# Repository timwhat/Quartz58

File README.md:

# Quartz58

Attempt at a two places removed, no compromises keyboard

Inspired by the lily58, SoflePLUS2, and MANY others to fit my personal needs

## Images

### CAD

Exploded view of the CAD currently

### PCB

BASE!

### Schematic

The reason why I made this project was that I was always fascinated by keyboards, especially the ergonomic ones, and I just love designing things. So since this was my chance to try it, so I jumped at it!

## Features

### Key Features

- **58 keys**, each able to support at the same time, MX and Choc hotswap sockets!

- **Wireless**, with the power of a nice!nano clone and a 750mAh battery!

- **iPod-style Encoder** on the left side for any encoder needed jazz... (such as volume control)

- **Trackpad** on the right side, for any analog needed or gesture related jazz pt2... (such as precision or window management)

- **Gasket Mount**, for improved typing feel and acoustics

- **MagSafe Magnets**, for adjustable tenting and compatibility with existing MagSafe accessories!

- **nice!view and OLED Display Support** on both halves to show stats like battery life, WPM, connection status, etc...

## Development Log

See [JOURNAL.md](JOURNAL.md) for detailed development progress and decisions

## BOM

| Purchase Status | Part                                                          | Qty | Price/per (CAD) | Total      | Link                                                                                            | Shipping (CAD) | Notes                                                                                 |
| --------------- | ------------------------------------------------------------- | --- | --------------- | ---------- | ----------------------------------------------------------------------------------------------- | -------------- | ------------------------------------------------------------------------------------- |
| x               | 10cm 10p 0.5mm pitch 10PCS FPC FFC Ribbon Flexible Flat Cable | 1   | 7.45            | 7.45       | [link](https://www.aliexpress.com/item/1005006420267064.html)                                   | 0              |                                                                                       |
| x               | 10cm 6p 0.5mm pitch 10PCS FPC FFC Ribbon Flexible Flat Cable  | 1   | 7.44            | 7.44       | [link](https://www.aliexpress.com/item/1005006420267064.html)                                   | 0              |                                                                                       |
| x               | Breakable Stackable PCB IC Crystal Socket Connector (for mcu) | 1   | 3.66            | 3.66       | [link](https://www.aliexpress.com/item/4001122376295.html)                                      | 0              |                                                                                       |
| x               | Nice View                                                     | 1   | 23.58           | 23.58      | [link](https://www.aliexpress.com/item/1005008115497843.html)                                   | 0              |                                                                                       |
| x               | 6 pin FFC FPC Connector 0.5 (10 per pack)                     | 1   | 2.05            | 2.05       | [link](https://www.aliexpress.com/item/10000348360254.html)                                     | 0              |                                                                                       |
| x               | 10 pin FFC FPC Connector 0.5 (10 per pack)                    | 1   | 2.06            | 2.06       | [link](https://www.aliexpress.com/item/10000348360254.html)                                     | 0              |                                                                                       |
| x               | Kailh Hot-swappable PCB Socket Hot Plug                       | 1   | 5.89            | 5.89       | [link](https://www.aliexpress.com/item/1005007225352311.html)                                   | 0              | Already have 20                                                                       |
| x               | M2 (OD3.2mm) 50pcs x 2mm                                      | 1   | 3.02            | 3.02       | [link](https://www.aliexpress.com/item/1005005220632314.html)                                   | 0              |                                                                                       |
| x               | White Blank MDA keycap set                                    | 1   | 37.79           | 37.79      | [link](https://www.aliexpress.com/item/1005007747757142.html)                                   | 0              |                                                                                       |
| x               | Reset Button                                                  | 1   | 3.21            | 3.21       | [link](https://www.aliexpress.com/item/33032223116.html)                                        | 0              |                                                                                       |
| x               | Power Switch                                                  | 1   | 3.07            | 3.07       | [link](https://www.aliexpress.com/item/4000685483225.html)                                      | 0              |                                                                                       |
| x               | Battery Jack (5 per pack)                                     | 1   | 1.79            | 1.79       | [link](https://www.aliexpress.com/item/1005002564191148.html)                                   | 0              | Used this for increased flexibility in use in the keyboard instead of the normal jack |
| x               | Magsafe Magnet Rings 15 plus version (2 per pack)             | 1   | 5.49            | 5.49       | [link](https://www.aliexpress.com/item/1005006981590979.html)                                   | 0              |                                                                                       |
| x               | 404090 2000mAh Battery                                        | 2   | 7.49            | 14.98      | [link](https://www.aliexpress.com/item/1005009607827493.html?mp=1)                              | 10.27          |                                                                                       |
| x               | TPS65-201A-S                                                  | 1   | 8.93            | 8.93       | [link](https://www.mouser.ca/ProductDetail/Azoteq/TPS65-201A-S?qs=pfd5qewlna5Lh8O0E8DcUQ%3D%3D) | 20             |                                                                                       |
| x               | PCB from JLCPCB                                               | 1   | 23.45           | 23.45      | [link](https://cart.jlcpcb.com/quote?rand=0.04393028142638511)                                  | 16.54          |                                                                                       |
|                 |                                                               |     |                 |            |                                                                                                 |                |                                                                                       |
|                 | **Subtotal:**                                                 |     | **CAD:**        | **153.86** |                                                                                                 | **46.81**      |                                                                                       |
|                 |                                                               |     | USD             | 111.21     |                                                                                                 | 33.84          |                                                                                       |
|                 |                                                               |     | **Total:**      | **145.05** |                                                                                                 |                | Will make up the difference if there are any hidden costs                             |
|                 |                                                               |     |                 |            |                                                                                                 |                |                                                                                       |

### Stuff I will buy

| Purchase Status | Part                                             | Qty | Price/per (CAD) | Total | Link                                                               | Shipping (CAD) | Notes |
| --------------- | ------------------------------------------------ | --- | --------------- | ----- | ------------------------------------------------------------------ | -------------- | ----- |
| x               | 20 PCS 2MM Thick Mechanical Keyboard Gasket      | 1   | 7.4             | 7.4   | [link](https://www.aliexpress.com/item/1005004800667967.html)      | 0              |       |
|                 | TTC Frozen V2 Switch Silent Linear (60 per pack) | 1   | 36.58           | 36.58 | [link](https://www.aliexpress.com/item/1005008909952057.html)      | 0              |       |
|                 | M2x16mm Hex Socket Head Cap                      | 1   | 2.9             | 2.9   | [link](http://www.aliexpress.com/item/32810872544.html)            | 0              |       |
| x               | NRF52840                                         | 2   | 4.32            | 8.64  | [link](https://www.aliexpress.com/item/1005006271779544.html?mp=1) | 0              |       |
| x               | SOD-123                                          | 1   | 2.79            | 2.79  | [link](https://www.aliexpress.com/item/1005006323468521.html)      | 0              |       |

### These are the stuff that I will get at a later date

| Part           | Qty | Price/per (CAD) | Total | Link  | Shipping (CAD) | Notes                                                     |
| -------------- | --- | --------------- | ----- | ----- | -------------- | --------------------------------------------------------- |
| TSWB3NCB111LFS | 1   | 14.54           | 14.54 | XCMKB | 48.48          | This is a custom order to them as they ship from malasyia |

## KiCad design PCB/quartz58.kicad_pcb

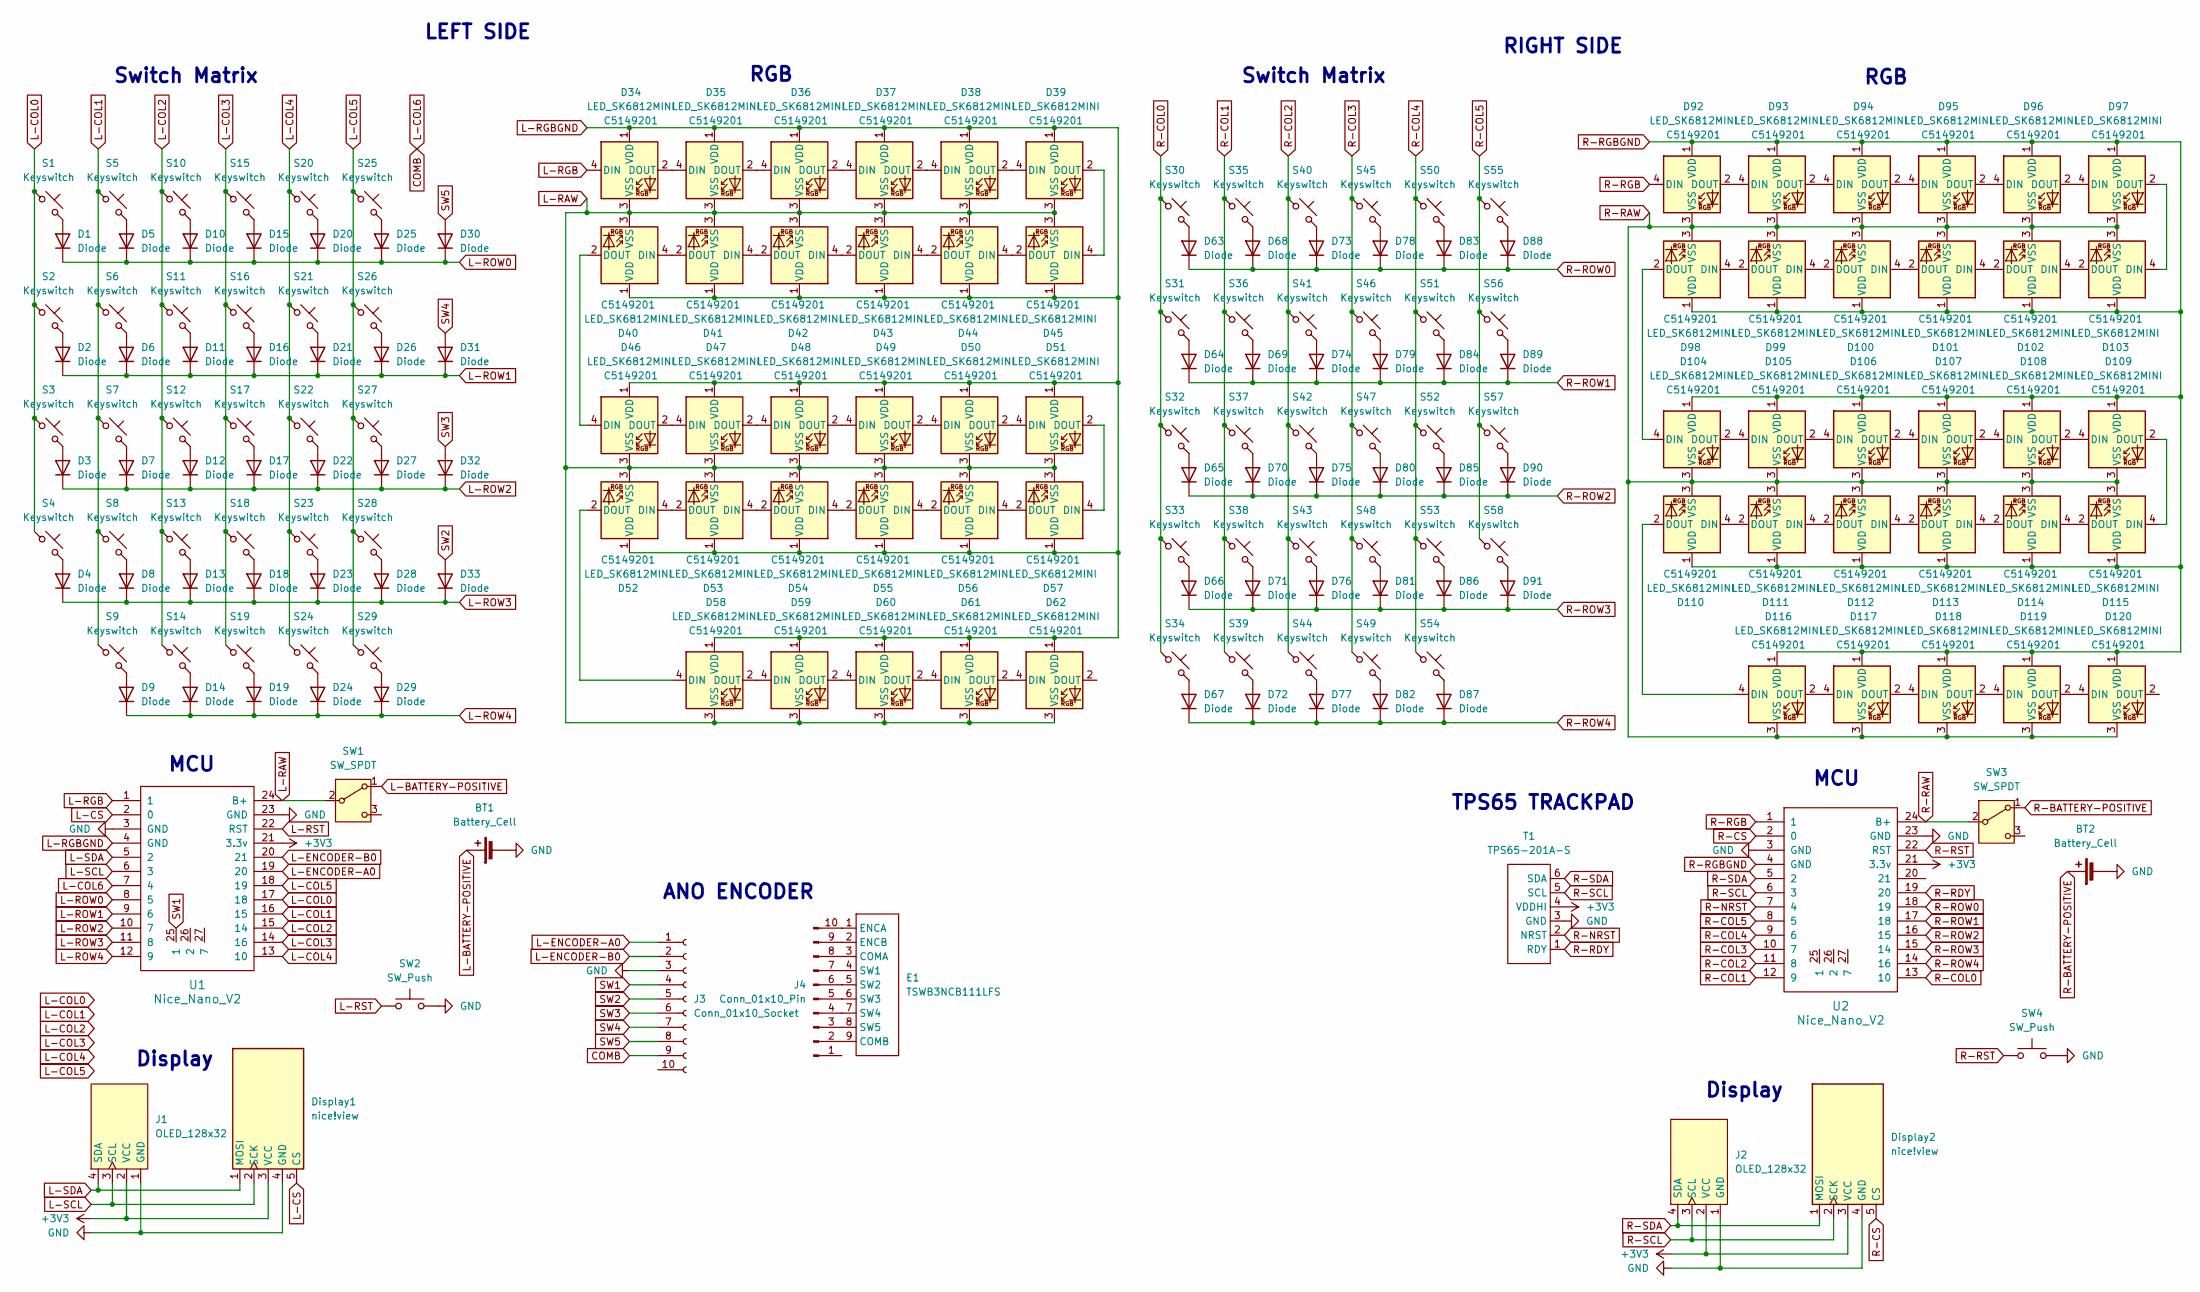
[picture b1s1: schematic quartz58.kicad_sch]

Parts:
BT1, BT2: Battery_Cell; JST_PH_S2B-PH-K_1x02_P2.00mm_Horizontal
D1, D2, D3, D4, D5, D6, D7, D8, D9, D10, D11, D12, D13, D14, D15, D16, D17, D18, D19, D20, D21, D22, D23, D24, D25, D26, D27, D28, D29, D30, D31, D32, D33, D63, D64, D65, D66, D67, D68, D69, D70, D71, D72, D73, D74, D75, D76, D77, D78, D79, D80, D81, D82, D83, D84, D85, D86, D87, D88, D89, D90, D91: Diode; Diode_SOD-123
D34, D35, D36, D37, D38, D39, D40, D41, D42, D43, D44, D45, D46, D47, D48, D49, D50, D51, D52, D53, D54, D55, D56, D57, D58, D59, D60, D61, D62, D92, D93, D94, D95, D96, D97, D98, D99, D100, D101, D102, D103, D104, D105, D106, D107, D108, D109, D110, D111, D112, D113, D114, D115, D116, D117, D118, D119, D120: LED_SK6812MINI; SK6812-MINI-E; LCSC C5149201
Display1, Display2: nice!view; nice_view
E1: TSWB3NCB111LFS; Encoder_TSWB3NCB111LFS
J1, J2: OLED_128x32
J3: Conn_01x10_Socket; Hirose_FH12-10S-0.5SH_1x10-1MP_P0.50mm_Horizontal
J4: Conn_01x10_Pin; Hirose_FH12-10S-0.5SH_1x10-1MP_P0.50mm_Horizontal
S1, S2, S3, S4, S5, S6, S7, S8, S9, S10, S11, S12, S13, S14, S15, S16, S17, S18, S19, S20, S21, S22, S23, S24, S25, S26, S27, S28, S29, S30, S31, S32, S33, S34, S35, S36, S37, S38, S39, S40, S41, S42, S43, S44, S45, S46, S47, S48, S49, S50, S51, S52, S53, S54, S55, S56, S57, S58: Keyswitch; Hotswap_Choc_V1V2
SW1, SW3: SW_SPDT; SW_SSSS811101
SW2, SW4: SW_Push; SW_EVQPUJ_4P7X3P5_PAN
T1: TPS65-201A-S; Hirose_FH12-6S-0.5SH_1x06-1MP_P0.50mm_Horizontal
U1, U2: Nice_Nano_V2; Nice_Nano_V2_Flipped

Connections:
+3V3: Display1.3 (VCC), Display2.3 (VCC), J1.2 (VCC), J2.2 (VCC), T1.4 (VDDHI), U1.21 (3.3v), U2.21 (3.3v)
COMB: J3.9, U1.7 (4)
GND: BT1.2 (-), BT2.2 (-), Display1.4 (GND), Display2.4 (GND), J1.1 (GND), J2.1 (GND), J3.3, SW2.2, SW4.2, T1.3 (GND), U1.3 (GND), U1.23 (GND), U2.3 (GND), U2.23 (GND)
L-BATTERY-POSITIVE: BT1.1 (+), SW1.1 (A)
L-COL0: S1.1, S2.1, S3.1, S4.1, U1.17 (18)
L-COL1: S5.1, S6.1, S7.1, S8.1, S9.1, U1.16 (15)
L-COL2: S10.1, S11.1, S12.1, S13.1, S14.1, U1.15 (14)
L-COL3: S15.1, S16.1, S17.1, S18.1, S19.1, U1.14 (16)
L-COL4: S20.1, S21.1, S22.1, S23.1, S24.1, U1.13 (10)
L-COL5: S25.1, S26.1, S27.1, S28.1, S29.1, U1.18 (19)
L-CS: Display1.5 (CS), U1.2 (0)
L-ENCODER-A0: J3.1, U1.19 (20)
L-ENCODER-B0: J3.2, U1.20 (21)
L-RAW: D34.3 (VSS), D35.3 (VSS), D36.3 (VSS), D37.3 (VSS), D38.3 (VSS), D39.3 (VSS), D40.3 (VSS), D41.3 (VSS), D42.3 (VSS), D43.3 (VSS), D44.3 (VSS), D45.3 (VSS), D46.3 (VSS), D47.3 (VSS), D48.3 (VSS), D49.3 (VSS), D50.3 (VSS), D51.3 (VSS), D52.3 (VSS), D53.3 (VSS), D54.3 (VSS), D55.3 (VSS), D56.3 (VSS), D57.3 (VSS), D58.3 (VSS), D59.3 (VSS), D60.3 (VSS), D61.3 (VSS), D62.3 (VSS), SW1.2 (B), U1.24 (B+)
L-RGB: D34.4 (DIN), U1.1
L-RGBGND: D34.1 (VDD), D35.1 (VDD), D36.1 (VDD), D37.1 (VDD), D38.1 (VDD), D39.1 (VDD), D40.1 (VDD), D41.1 (VDD), D42.1 (VDD), D43.1 (VDD), D44.1 (VDD), D45.1 (VDD), D46.1 (VDD), D47.1 (VDD), D48.1 (VDD), D49.1 (VDD), D50.1 (VDD), D51.1 (VDD), D52.1 (VDD), D53.1 (VDD), D54.1 (VDD), D55.1 (VDD), D56.1 (VDD), D57.1 (VDD), D58.1 (VDD), D59.1 (VDD), D60.1 (VDD), D61.1 (VDD), D62.1 (VDD), U1.4 (GND)
L-ROW0: D1.1 (K), D5.1 (K), D10.1 (K), D15.1 (K), D20.1 (K), D25.1 (K), D30.1 (K), U1.8 (5)
L-ROW1: D2.1 (K), D6.1 (K), D11.1 (K), D16.1 (K), D21.1 (K), D26.1 (K), D31.1 (K), U1.9 (6)
L-ROW2: D3.1 (K), D7.1 (K), D12.1 (K), D17.1 (K), D22.1 (K), D27.1 (K), D32.1 (K), U1.10 (7)
L-ROW3: D4.1 (K), D8.1 (K), D13.1 (K), D18.1 (K), D23.1 (K), D28.1 (K), D33.1 (K), U1.11 (8)
L-ROW4: D9.1 (K), D14.1 (K), D19.1 (K), D24.1 (K), D29.1 (K), U1.12 (9)
L-RST: SW2.1, U1.22 (RST)
L-SCL: Display1.2 (SCK), J1.3 (SCL), U1.6 (3)
L-SDA: Display1.1 (MOSI), J1.4 (SDA), U1.5 (2)
unnamed: D1.2 (A), S1.2
unnamed: D2.2 (A), S2.2
unnamed: D3.2 (A), S3.2
unnamed: D4.2 (A), S4.2
unnamed: D5.2 (A), S5.2
unnamed: D6.2 (A), S6.2
unnamed: D7.2 (A), S7.2
unnamed: D8.2 (A), S8.2
unnamed: D9.2 (A), S9.2
unnamed: D10.2 (A), S10.2
unnamed: D11.2 (A), S11.2
unnamed: D12.2 (A), S12.2
unnamed: D13.2 (A), S13.2
unnamed: D14.2 (A), S14.2
unnamed: D15.2 (A), S15.2
unnamed: D16.2 (A), S16.2
unnamed: D17.2 (A), S17.2
unnamed: D18.2 (A), S18.2
unnamed: D19.2 (A), S19.2
unnamed: D20.2 (A), S20.2
unnamed: D21.2 (A), S21.2
unnamed: D22.2 (A), S22.2
unnamed: D23.2 (A), S23.2
unnamed: D24.2 (A), S24.2
unnamed: D25.2 (A), S25.2
unnamed: D26.2 (A), S26.2
unnamed: D27.2 (A), S27.2
unnamed: D28.2 (A), S28.2
unnamed: D29.2 (A), S29.2
unnamed: D34.2 (DOUT), D35.4 (DIN)
unnamed: D35.2 (DOUT), D36.4 (DIN)
unnamed: D36.2 (DOUT), D37.4 (DIN)
unnamed: D37.2 (DOUT), D38.4 (DIN)
unnamed: D38.2 (DOUT), D39.4 (DIN)
unnamed: D39.2 (DOUT), D45.4 (DIN)
unnamed: D40.4 (DIN), D41.2 (DOUT)
unnamed: D40.2 (DOUT), D46.4 (DIN)
unnamed: D41.4 (DIN), D42.2 (DOUT)
unnamed: D42.4 (DIN), D43.2 (DOUT)
unnamed: D43.4 (DIN), D44.2 (DOUT)
unnamed: D44.4 (DIN), D45.2 (DOUT)
unnamed: D46.2 (DOUT), D47.4 (DIN)
unnamed: D47.2 (DOUT), D48.4 (DIN)
unnamed: D48.2 (DOUT), D49.4 (DIN)
unnamed: D49.2 (DOUT), D50.4 (DIN)
unnamed: D50.2 (DOUT), D51.4 (DIN)
unnamed: D51.2 (DOUT), D57.4 (DIN)
unnamed: D52.4 (DIN), D53.2 (DOUT)
unnamed: D52.2 (DOUT), D58.4 (DIN)
unnamed: D53.4 (DIN), D54.2 (DOUT)
unnamed: D54.4 (DIN), D55.2 (DOUT)
unnamed: D55.4 (DIN), D56.2 (DOUT)
unnamed: D56.4 (DIN), D57.2 (DOUT)
unnamed: D58.2 (DOUT), D59.4 (DIN)
unnamed: D59.2 (DOUT), D60.4 (DIN)
unnamed: D60.2 (DOUT), D61.4 (DIN)
unnamed: D61.2 (DOUT), D62.4 (DIN)
unnamed: D63.2 (A), S30.2
unnamed: D64.2 (A), S31.2
unnamed: D65.2 (A), S32.2
unnamed: D66.2 (A), S33.2
unnamed: D67.2 (A), S34.2
unnamed: D68.2 (A), S35.2
unnamed: D69.2 (A), S36.2
unnamed: D70.2 (A), S37.2
unnamed: D71.2 (A), S38.2
unnamed: D72.2 (A), S39.2
unnamed: D73.2 (A), S40.2
unnamed: D74.2 (A), S41.2
unnamed: D75.2 (A), S42.2
unnamed: D76.2 (A), S43.2
unnamed: D77.2 (A), S44.2
unnamed: D78.2 (A), S45.2
unnamed: D79.2 (A), S46.2
unnamed: D80.2 (A), S47.2
unnamed: D81.2 (A), S48.2
unnamed: D82.2 (A), S49.2
unnamed: D83.2 (A), S50.2
unnamed: D84.2 (A), S51.2
unnamed: D85.2 (A), S52.2
unnamed: D86.2 (A), S53.2
unnamed: D87.2 (A), S54.2
unnamed: D88.2 (A), S55.2
unnamed: D89.2 (A), S56.2
unnamed: D90.2 (A), S57.2
unnamed: D91.2 (A), S58.2
unnamed: D92.2 (DOUT), D93.4 (DIN)
unnamed: D93.2 (DOUT), D94.4 (DIN)
unnamed: D94.2 (DOUT), D95.4 (DIN)
unnamed: D95.2 (DOUT), D96.4 (DIN)
unnamed: D96.2 (DOUT), D97.4 (DIN)
unnamed: D98.4 (DIN), D99.2 (DOUT)
unnamed: D100.4 (DIN), D101.2 (DOUT)
unnamed: D99.4 (DIN), D100.2 (DOUT)
unnamed: D101.4 (DIN), D102.2 (DOUT)
unnamed: D102.4 (DIN), D103.2 (DOUT)
unnamed: D97.2 (DOUT), D103.4 (DIN)
unnamed: D98.2 (DOUT), D104.4 (DIN)
unnamed: D104.2 (DOUT), D105.4 (DIN)
unnamed: D105.2 (DOUT), D106.4 (DIN)
unnamed: D106.2 (DOUT), D107.4 (DIN)
unnamed: D107.2 (DOUT), D108.4 (DIN)
unnamed: D108.2 (DOUT), D109.4 (DIN)
unnamed: D109.2 (DOUT), D115.4 (DIN)
unnamed: D110.4 (DIN), D111.2 (DOUT)
unnamed: D110.2 (DOUT), D116.4 (DIN)
unnamed: D111.4 (DIN), D112.2 (DOUT)
unnamed: D112.4 (DIN), D113.2 (DOUT)
unnamed: D113.4 (DIN), D114.2 (DOUT)
unnamed: D114.4 (DIN), D115.2 (DOUT)
unnamed: D116.2 (DOUT), D117.4 (DIN)
unnamed: D117.2 (DOUT), D118.4 (DIN)
unnamed: D118.2 (DOUT), D119.4 (DIN)
unnamed: D119.2 (DOUT), D120.4 (DIN)
unnamed: E1.3 (COMA), J4.8
unnamed: E1.9 (COMB), J4.2
unnamed: E1.1 (ENCA), J4.10
unnamed: E1.2 (ENCB), J4.9
unnamed: E1.4 (SW1), J4.7
unnamed: E1.5 (SW2), J4.6
unnamed: E1.6 (SW3), J4.5
unnamed: E1.7 (SW4), J4.4
unnamed: E1.8 (SW5), J4.3
R-BATTERY-POSITIVE: BT2.1 (+), SW3.1 (A)
R-COL0: S30.1, S31.1, S32.1, S33.1, S34.1, U2.13 (10)
R-COL1: S35.1, S36.1, S37.1, S38.1, S39.1, U2.12 (9)
R-COL2: S40.1, S41.1, S42.1, S43.1, S44.1, U2.11 (8)
R-COL3: S45.1, S46.1, S47.1, S48.1, S49.1, U2.10 (7)
R-COL4: S50.1, S51.1, S52.1, S53.1, S54.1, U2.9 (6)
R-COL5: S55.1, S56.1, S57.1, S58.1, U2.8 (5)
R-CS: Display2.5 (CS), U2.2 (0)
R-NRST: T1.2 (NRST), U2.7 (4)
R-RAW: D92.3 (VSS), D93.3 (VSS), D94.3 (VSS), D95.3 (VSS), D96.3 (VSS), D97.3 (VSS), D98.3 (VSS), D99.3 (VSS), D100.3 (VSS), D101.3 (VSS), D102.3 (VSS), D103.3 (VSS), D104.3 (VSS), D105.3 (VSS), D106.3 (VSS), D107.3 (VSS), D108.3 (VSS), D109.3 (VSS), D110.3 (VSS), D111.3 (VSS), D112.3 (VSS), D113.3 (VSS), D114.3 (VSS), D115.3 (VSS), D116.3 (VSS), D117.3 (VSS), D118.3 (VSS), D119.3 (VSS), D120.3 (VSS), SW3.2 (B), U2.24 (B+)
R-RDY: T1.1 (RDY), U2.19 (20)
R-RGB: D92.4 (DIN), U2.1
R-RGBGND: D92.1 (VDD), D93.1 (VDD), D94.1 (VDD), D95.1 (VDD), D96.1 (VDD), D97.1 (VDD), D98.1 (VDD), D99.1 (VDD), D100.1 (VDD), D101.1 (VDD), D102.1 (VDD), D103.1 (VDD), D104.1 (VDD), D105.1 (VDD), D106.1 (VDD), D107.1 (VDD), D108.1 (VDD), D109.1 (VDD), D110.1 (VDD), D111.1 (VDD), D112.1 (VDD), D113.1 (VDD), D114.1 (VDD), D115.1 (VDD), D116.1 (VDD), D117.1 (VDD), D118.1 (VDD), D119.1 (VDD), D120.1 (VDD), U2.4 (GND)
R-ROW0: D63.1 (K), D68.1 (K), D73.1 (K), D78.1 (K), D83.1 (K), D88.1 (K), U2.18 (19)
R-ROW1: D64.1 (K), D69.1 (K), D74.1 (K), D79.1 (K), D84.1 (K), D89.1 (K), U2.17 (18)
R-ROW2: D65.1 (K), D70.1 (K), D75.1 (K), D80.1 (K), D85.1 (K), D90.1 (K), U2.16 (15)
R-ROW3: D66.1 (K), D71.1 (K), D76.1 (K), D81.1 (K), D86.1 (K), D91.1 (K), U2.15 (14)
R-ROW4: D67.1 (K), D72.1 (K), D77.1 (K), D82.1 (K), D87.1 (K), U2.14 (16)
R-RST: SW4.1, U2.22 (RST)
R-SCL: Display2.2 (SCK), J2.3 (SCL), T1.5 (SCL), U2.6 (3)
R-SDA: Display2.1 (MOSI), J2.4 (SDA), T1.6 (SDA), U2.5 (2)
SW1: J3.4, U1.25 (1)
SW2: D33.2 (A), J3.5
SW3: D32.2 (A), J3.6
SW4: D31.2 (A), J3.7
SW5: D30.2 (A), J3.8

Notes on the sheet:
TPS65 TRACKPAD
Display
MCU
ANO ENCODER
RIGHT SIDE
Switch Matrix
RGB
LEFT SIDE

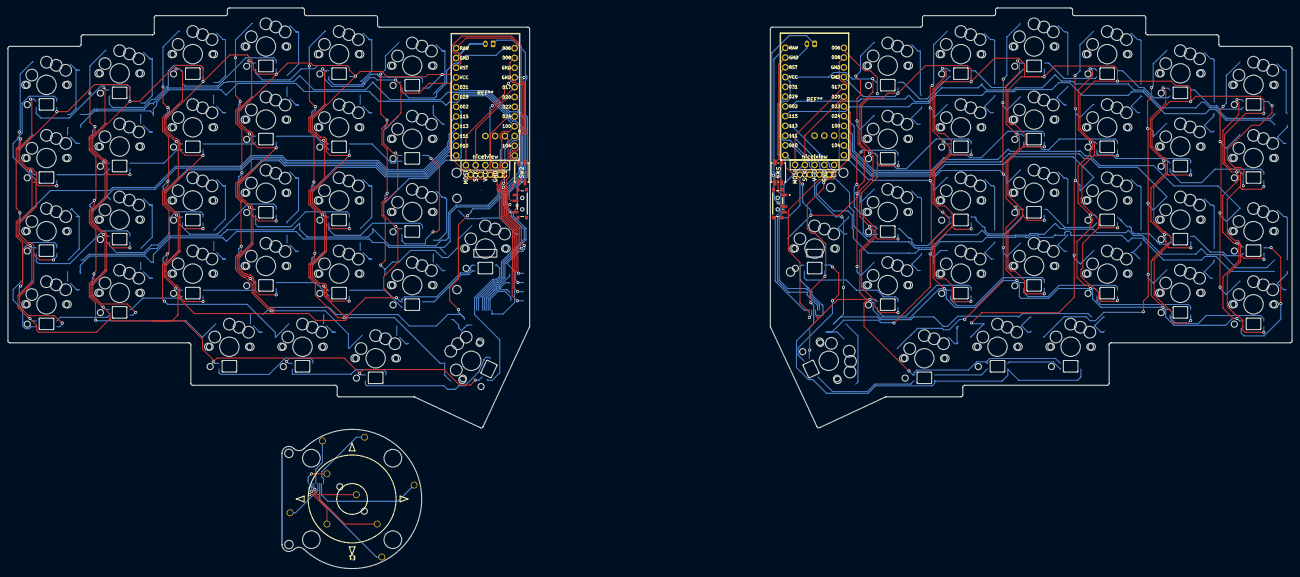
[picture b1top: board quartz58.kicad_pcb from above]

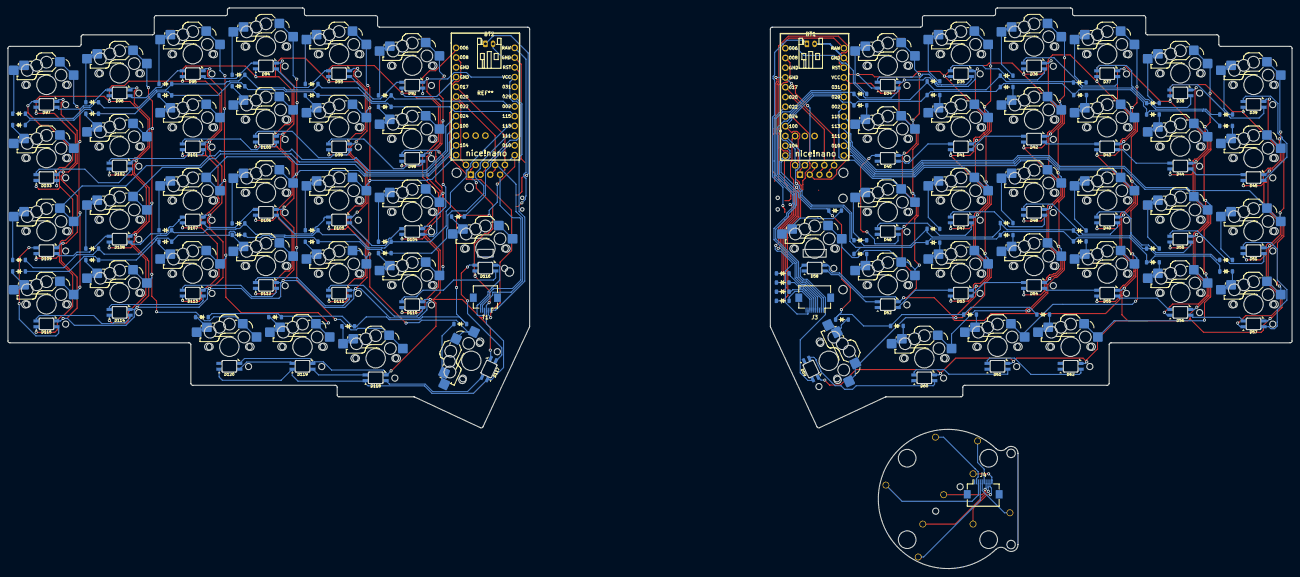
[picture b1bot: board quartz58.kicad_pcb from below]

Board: 2 copper layers, 334.3 x 145.9 mm, 194 parts (127 on the bottom side), 173 nets.

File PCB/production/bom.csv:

Designator,Footprint,Quantity,Value,LCSC Part #
"BT1, BT2",JST_PH_S2B-PH-K_1x02_P2.00mm_Horizontal,2,Battery_Cell,
"D1, D10, D11, D12, D13, D14, D15, D16, D17, D18, D19, D2, D20, D21, D22, D23, D24, D25, D26, D27, D28, D29, D3, D30, D31, D32, D33, D4, D5, D6, D63, D64, D65, D66, D67, D68, D69, D7, D70, D71, D72, D73, D74, D75, D76, D77, D78, D79, D8, D80, D81, D82, D83, D84, D85, D86, D87, D88, D89, D9, D90, D91",Diode_SOD-123,62,Diode,
"DISPLAY1, DISPLAY2",nice_view,2,nice!view,
E1,Encoder_TSWB3NCB111LFS,1,TSWB3NCB111LFS,
"J1, J2",OLED_128x32,2,OLED_128x32,
J3,Hirose_FH12-10S-0.5SH_1x10-1MP_P0.50mm_Horizontal,1,Conn_01x10_Socket,
J4,Hirose_FH12-10S-0.5SH_1x10-1MP_P0.50mm_Horizontal,1,Conn_01x10_Pin,
"S1, S10, S11, S12, S13, S14, S15, S16, S17, S18, S19, S2, S20, S21, S22, S23, S24, S25, S26, S27, S28, S29, S3, S30, S31, S32, S33, S34, S35, S36, S37, S38, S39, S4, S40, S41, S42, S43, S44, S45, S46, S47, S48, S49, S5, S50, S51, S52, S53, S54, S55, S56, S57, S58, S6, S7, S8, S9",Hotswap_Choc_MX_Combo,58,Keyswitch,
"SW1, SW3",SW_SSSS811101,2,SW_SPDT,
"SW2, SW4",SW_EVQPUJ_4P7X3P5_PAN,2,SW_Push,
T1,Hirose_FH12-6S-0.5SH_1x06-1MP_P0.50mm_Horizontal,1,TPS65-201A-S,
"U1, U2",nice_nano,2,Nice_Nano_V2,

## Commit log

2025-07-15 True Beginning
2025-07-15 additions to PCB and journal
2025-07-15 .gitingore and readme additions
2025-07-15 minor changes
2025-07-17 small progress on left
2025-07-18 easy stuff on pcb done
2025-07-18 minor formatting improvements
2025-07-19 todays progress, learned how to create symbols
2025-07-20 more progress?
2025-07-24 coming back
2025-07-24 minor change to formatting
2025-07-25 pcb and cad updates
2025-07-25 minor change
2025-07-25 minor spelling fix
2025-07-27 todays progress
2025-07-27 updates to pcb
2025-07-29 might be cooked chat
2025-07-31 more progress
2025-07-31 left side ready for review
2025-08-01 minor chagne
2025-08-01 cad so far upload
2025-08-01 BOM upload
2025-08-01 addition to total time spend
2025-08-01 gerbers upload
2025-08-01 finished for the night
2025-08-01 zmk path addition
2025-08-01 final one trust
2025-08-01 minor BOM total fix
2025-08-01 forgot fpc ribibon cables
2025-08-01 slight update
2025-08-01 updates to jst connector
2025-08-01 update to gerbers
2025-08-01 minor grammar fixes in README.md
2025-08-02 calc error fix
2025-08-02 spreadsheet update
2025-08-02 minor fomatting changes
2025-08-03 BOM and Schem updates
2025-08-04 updates to pcb and BOM
2025-08-04 update to readme with BOM and features
2025-08-05 pain
2025-08-05 better key feautes list
2025-08-06 basically there
2025-08-06 more updates
2025-08-06 updates to readme
2025-08-06 spelling grammar fix
2025-08-06 minor journal fix
2025-08-06 slight update to cad
2025-08-16 back kindof
2025-08-16 switching to jlcpcb plugin for gerbers
2025-08-18 borderline, caught between the tides of pain and rapture
2025-08-18 3d raytracing view!
2025-08-22 minor fix
2025-08-23 cad polish
2025-08-23 bom optimizations
2025-08-23 socket change
2025-08-24 minor item change
2025-08-25 yeaa
2025-08-26 minor image addition
2025-08-26 orderedd
2025-08-26 minro fix
2025-09-04 Remove placeholder ZMK directory in preparation for submodule
2025-09-04 Add ZMK config as submodule
